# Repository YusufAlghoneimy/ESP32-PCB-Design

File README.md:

# ESP32-PCB-Design

4 Layer ESP32-PCB Design done in Kicad9

Reference:
ESP32 datasheet: (https://cdn.sparkfun.com/datasheets/IoT/esp32_datasheet_en.pdf)

Youtube PCB reference: made by morten (https://www.youtube.com/watch?v=b-7bMl6fJio&t=8320s)

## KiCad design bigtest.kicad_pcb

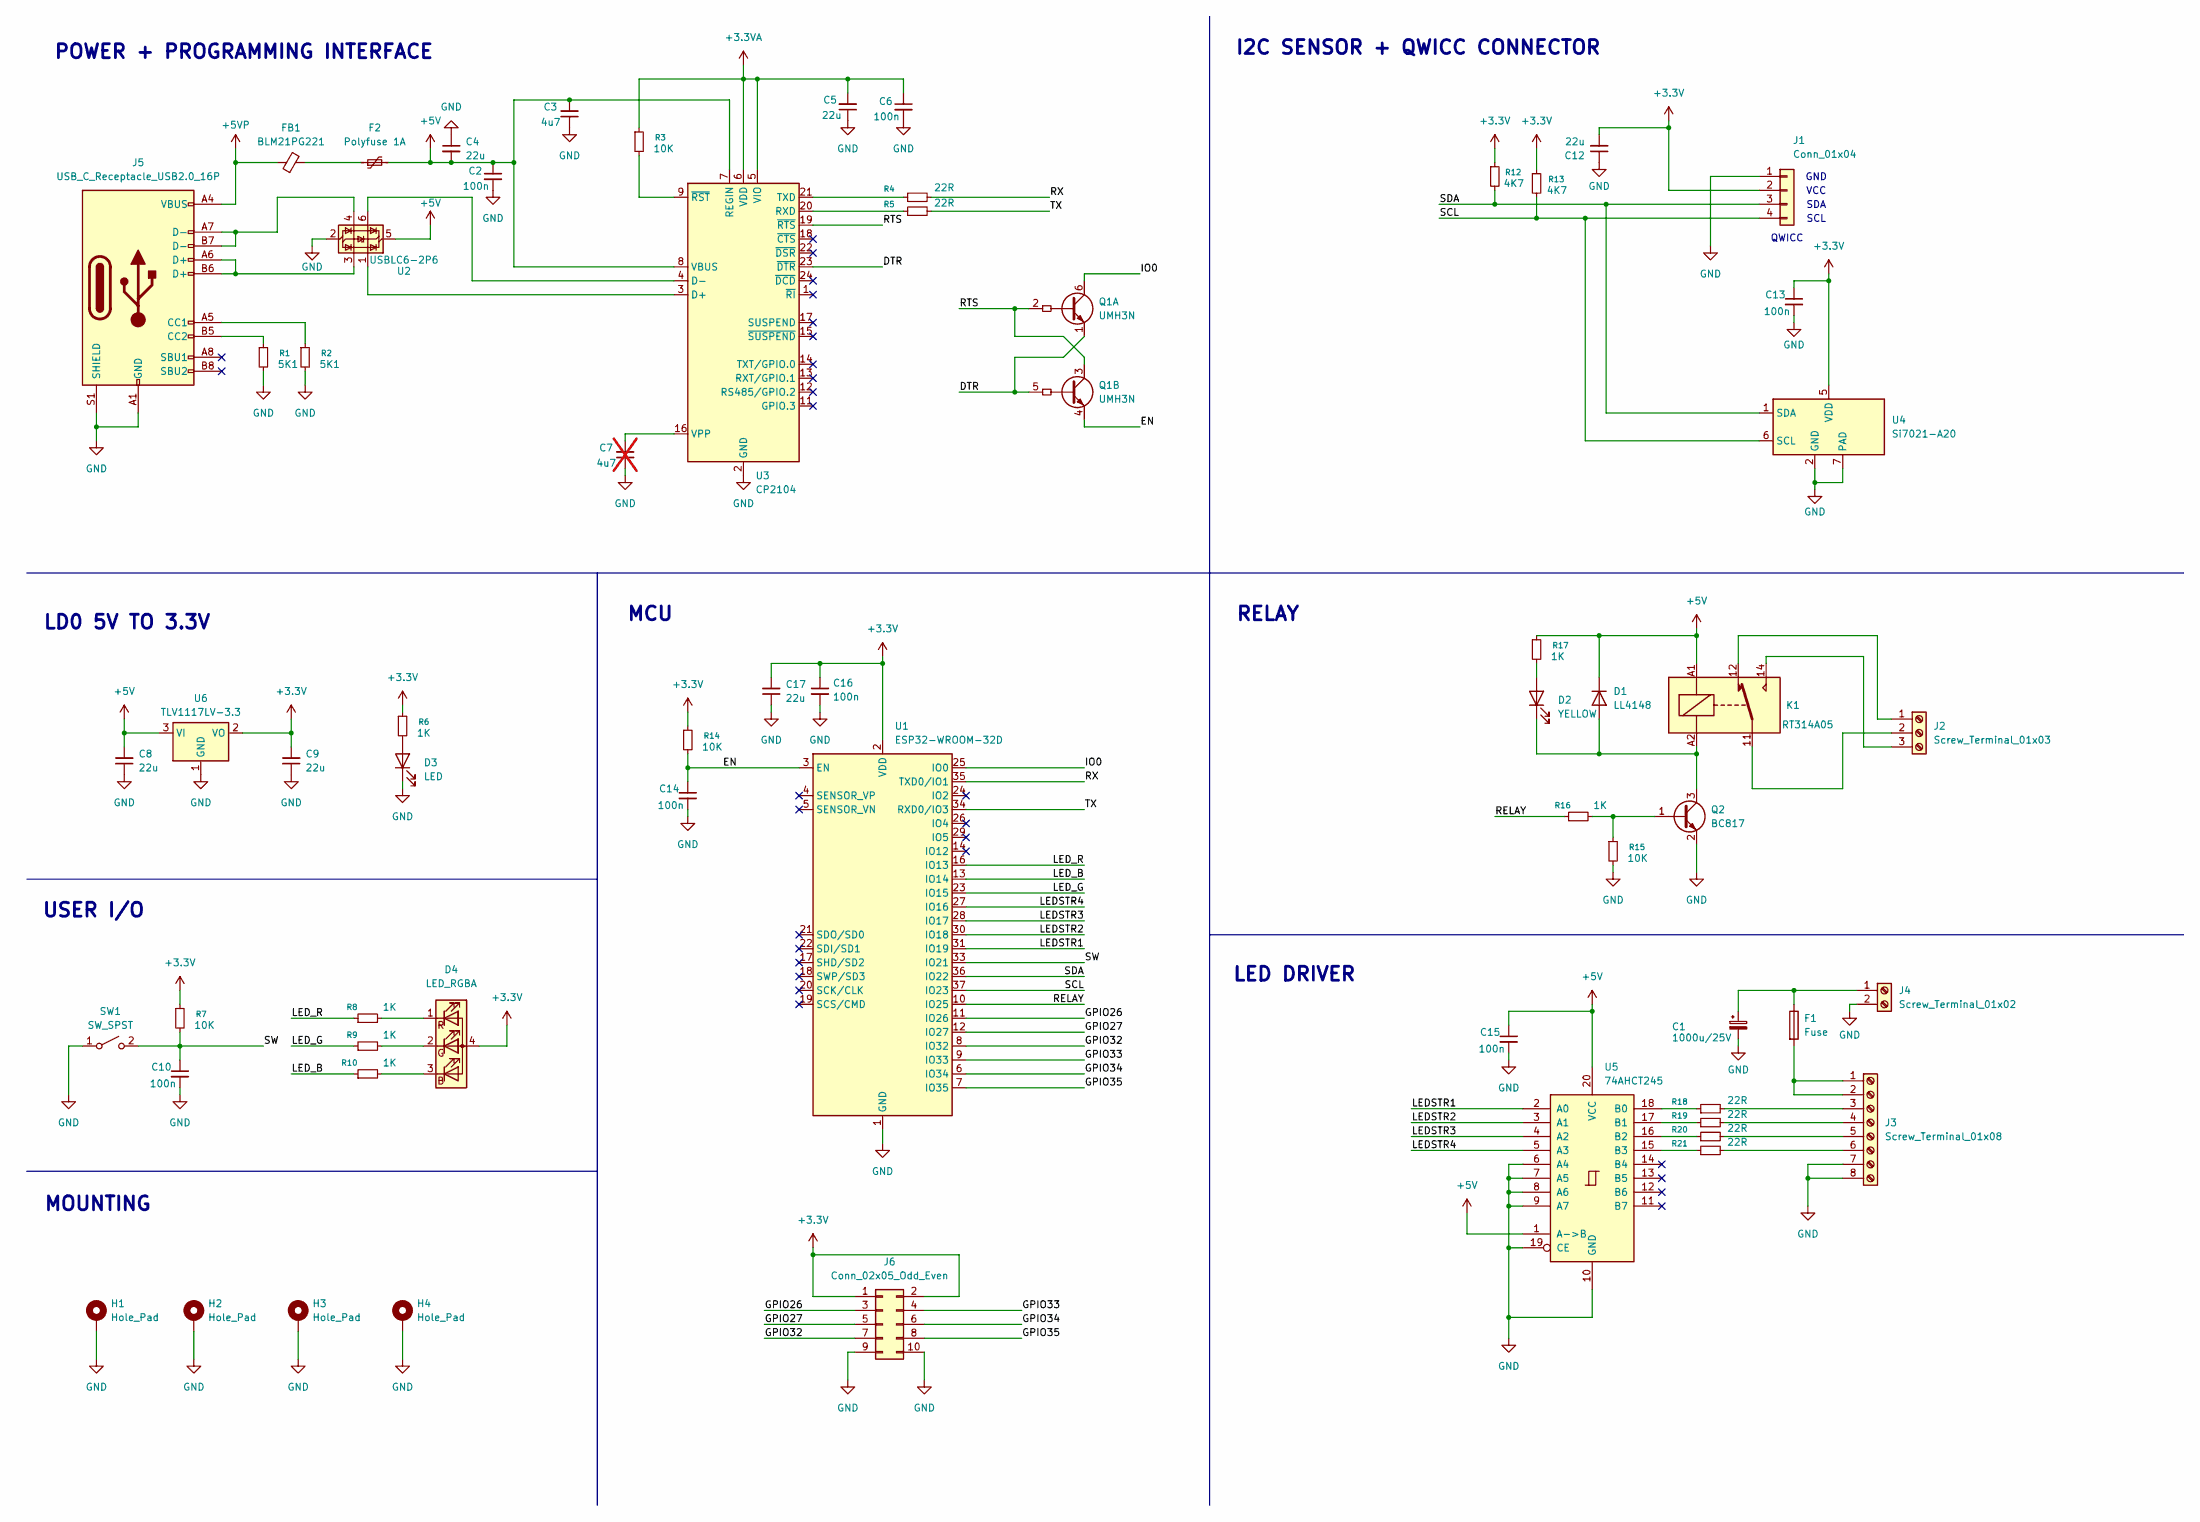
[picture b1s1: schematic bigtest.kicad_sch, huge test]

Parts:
C1: 1000u/25V; CP_Radial_D10.0mm_P5.00mm
C2, C6, C10, C13, C14, C15, C16: 100n; C_0402_1005Metric_Pad0.74x0.62mm_HandSolder
C3: 4u7; C_0805_2012Metric_Pad1.18x1.45mm_HandSolder
C4, C5, C8, C9, C12, C17: 22u; C_0805_2012Metric_Pad1.18x1.45mm_HandSolder
C7: 4u7; C_0805_2012Metric_Pad1.18x1.45mm_HandSolder; not fitted
D1: LL4148; D_MiniMELF
D2: YELLOW; LED_0603_1608Metric_Pad1.05x0.95mm_HandSolder
D3: LED; LED_0603_1608Metric_Pad1.05x0.95mm_HandSolder
D4: LED_RGBA; LED_RGB_Wuerth-PLCC4_3.2x2.8mm_150141M173100
F1: Fuse; Fuse_0402_1005Metric
F2: Polyfuse 1A; Fuse_1206_3216Metric_Pad1.42x1.75mm_HandSolder
FB1: BLM21PG221; L_0603_1608Metric_Pad1.05x0.95mm_HandSolder
H1, H2, H3, H4: Hole_Pad; MountingHole_3.2mm_M3_Pad_Via
J1: Conn_01x04; JST_SH_SM04B-SRSS-TB_1x04-1MP_P1.00mm_Horizontal
J2: Screw_Terminal_01x03; TerminalBlock_Phoenix_MKDS-3-3-5.08_1x03_P5.08mm_Horizontal
J3: Screw_Terminal_01x08; TerminalBlock_Phoenix_MKDS-1,5-8_1x08_P5.00mm_Horizontal
J4: Screw_Terminal_01x02; TerminalBlock_Phoenix_MKDS-1,5-2-5.08_1x02_P5.08mm_Horizont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
J5: USB_C_Receptacle_USB2.0_16P; USB_C_Receptacle_HRO_TYPE-C-31-M-12
J6: Conn_02x05_Odd_Even; PinHeader_2x05_P2.54mm_Vertical
K1: RT314A05; Relay_SPDT_Schrack-RT1-16A-FormC_RM5mm
Q1: UMH3N; SOT-363_SC-70-6
Q2: BC817; SOT-23
R1, R2: 5K1; R_0402_1005Metric_Pad0.72x0.64mm_HandSolder
R3, R7, R14, R15: 10K; R_0402_1005Metric_Pad0.72x0.64mm_HandSolder
R4, R5, R18, R19, R20, R21: 22R; R_0402_1005Metric_Pad0.72x0.64mm_HandSolder
R6, R8, R9, R10, R16, R17: 1K; R_0402_1005Metric_Pad0.72x0.64mm_HandSolder
R12, R13: 4K7; R_0402_1005Metric_Pad0.72x0.64mm_HandSolder
SW1: SW_SPST; SW_Push_1P1T_NO_CK_KSC7xxJ
U1: ESP32-WROOM-32D
U2: USBLC6-2P6; SOT-666
U3: CP2104; QFN-24-1EP_4x4mm_P0.5mm_EP2.6x2.6mm
U4: Si7021-A20; DFN-6-1EP_3x3mm_P1mm_EP1.5x2.4mm
U5: 74AHCT245; DIP-20_W7.62mm
U6: TLV1117LV-3.3; SOT-223-3_TabPin2

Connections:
+3.3V: C9.2, C12.2, C13.1, C16.1, C17.2, D4.4 (A), J1.2, J6.1, J6.2, R6.1, R7.1, R12.1, R13.1, R14.1, U1.2 (VDD), U4.5 (VDD), U6.2 (VO)
+3.3VA: C5.2, C6.1, R3.1, U3.5 (VIO), U3.6 (VDD)
+5V: C2.1, C3.2, C4.2, C8.2, C15.1, D1.1 (K), F2.2, K1.A1, R17.1, U2.5 (VBUS), U3.7 (REGIN), U3.8 (VBUS), U5.1 (A->B), U5.20 (VCC), U6.3 (VI)
+5VP: FB1.1, J5.A4 (VBUS), J5.A9 (VBUS), J5.B4 (VBUS), J5.B9 (VBUS)
/DTR: Q1.1 (E1), Q1.5 (B2), U3.23 (~DTR)
/EN: C14.1, Q1.4 (E2), R14.2, U1.3 (EN)
/GPIO26: J6.3, U1.11 (IO26)
/GPIO27: J6.5, U1.12 (IO27)
/GPIO32: J6.7, U1.8 (IO32)
/GPIO33: J6.4, U1.9 (IO33)
/GPIO34: J6.6, U1.6 (IO34)
/GPIO35: J6.8, U1.7 (IO35)
/IO0: Q1.6 (C1), U1.25 (IO0)
/LEDSTR1: U1.31 (IO19), U5.2 (A0)
/LEDSTR2: U1.30 (IO18), U5.3 (A1)
/LEDSTR3: U1.28 (IO17), U5.4 (A2)
/LEDSTR4: U1.27 (IO16), U5.5 (A3)
/LED_B: R10.1, U1.13 (IO14)
/LED_G: R9.1, U1.23 (IO15)
/LED_R: R8.1, U1.16 (IO13)
/RELAY: R16.1, U1.10 (IO25)
/RTS: Q1.2 (B1), Q1.3 (C2), U3.19 (~RTS)
/RX: R4.2, U1.35 (TXD0/IO1)
/SCL: J1.4, R13.2, U1.37 (IO23), U4.6 (SCL)
/SDA: J1.3, R12.2, U1.36 (IO22), U4.1 (SDA)
/SW: C10.1, R7.2, SW1.2 (B), U1.33 (IO21)
/TX: R5.2, U1.34 (RXD0/IO3)
GND: C1.2, C2.2, C3.1, C4.1, C5.1, C6.2, C7.1, C8.1, C9.1, C10.2, C12.1, C13.2, C14.2, C15.2, C16.2, C17.1, D3.1 (K), H1.1, H2.1, H3.1, H4.1, J1.1, J3.7, J3.8, J4.2, J5.A1 (GND), J5.A12 (GND), J5.B1 (GND), J5.B12 (GND), J5.S1 (SHIELD), J6.9, J6.10, Q2.2 (E), R1.2, R2.2, R15.2, SW1.1 (A), U1.1 (GND), U1.15 (GND), U1.38 (GND), U1.39 (GND), U2.2 (GND), U3.2 (GND), U3.25 (GND), U4.2 (GND), U4.7 (PAD), U5.6 (A4), U5.7 (A5), U5.8 (A6), U5.9 (A7), U5.10 (GND), U5.19 (CE), U6.1 (GND)
unnamed: D1.2 (A), D2.1 (K), K1.A2, Q2.3 (C)
unnamed: D2.2 (A), R17.2
unnamed: D3.2 (A), R6.2
unnamed: D4.3 (BK), R10.2
unnamed: D4.2 (GK), R9.2
unnamed: D4.1 (RK), R8.2
unnamed: F2.1, FB1.2
unnamed: J2.1, K1.12
unnamed: J2.2, K1.11
unnamed: J2.3, K1.14
unnamed: F1.2, J3.1, J3.2
unnamed: J3.3, R18.2
unnamed: J3.4, R19.2
unnamed: J3.5, R20.2
unnamed: J3.6, R21.2
unnamed: C1.1, F1.1, J4.1
unnamed: J5.A5 (CC1), R2.1
unnamed: J5.B5 (CC2), R1.1
unnamed: J5.A6 (D+), J5.B6 (D+), U2.3 (I/O2)
unnamed: J5.A7 (D-), J5.B7 (D-), U2.4 (I/O2)
unnamed: Q2.1 (B), R15.1, R16.2
unnamed: U2.1 (I/O1), U3.3 (D+)
unnamed: U2.6 (I/O1), U3.4 (D-)
unnamed: R5.1, U3.20 (RXD)
unnamed: R4.1, U3.21 (TXD)
unnamed: C7.2, U3.16 (VPP)
unnamed: R3.2, U3.9 (~RST)
unnamed: R18.1, U5.18 (B0)
unnamed: R19.1, U5.17 (B1)
unnamed: R20.1, U5.16 (B2)
unnamed: R21.1, U5.15 (B3)

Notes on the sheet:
RELAY
QWICC
LD0 5V TO 3.3V
POWER + PROGRAMMING INTERFACE
USER I/O
MCU
I2C SENSOR + QWICC CONNECTOR
VCC
SCL
MOUNTING
LED DRIVER
GND
SDA

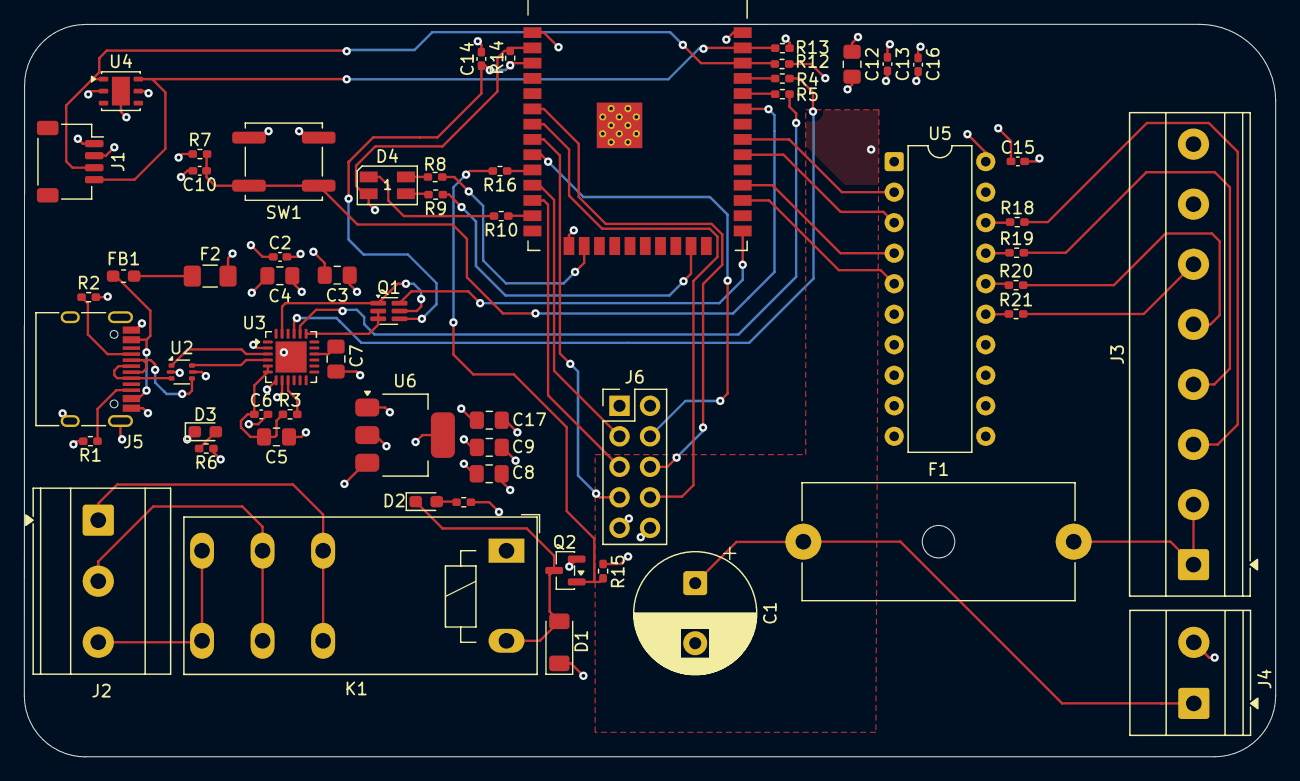
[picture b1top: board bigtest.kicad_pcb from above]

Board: 4 copper layers, 104.1 x 61.0 mm, 59 parts (0 on the bottom side), 59 nets.
